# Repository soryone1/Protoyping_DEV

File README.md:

# Protoyping_DEV
This is for Prototyping Electronic Devices

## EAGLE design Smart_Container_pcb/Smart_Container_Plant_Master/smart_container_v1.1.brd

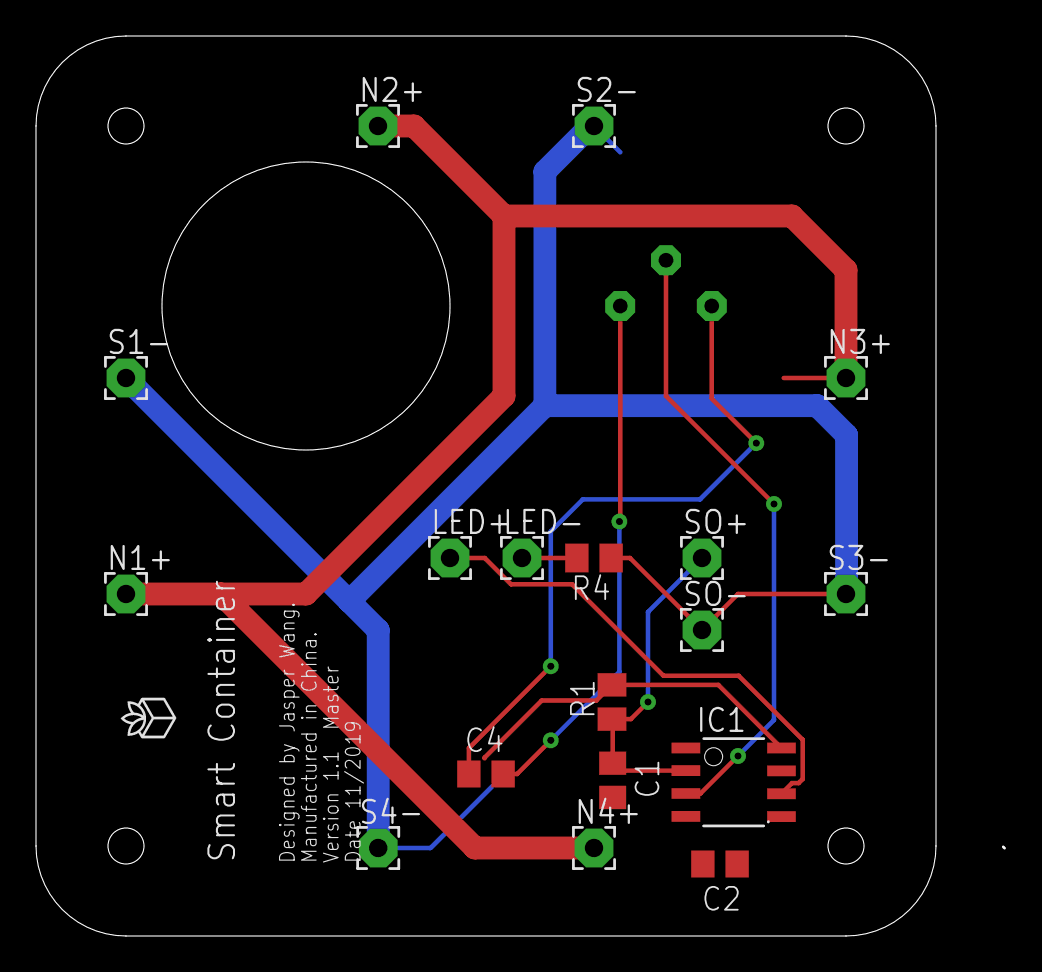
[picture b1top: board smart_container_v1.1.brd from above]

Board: 2 copper layers, 53.7 x 49.8 mm, 19 parts (1 on the bottom side), 9 nets.

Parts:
C1, C2, C4: 0.1uF; C0805
IC1: TINY13-20SSU; 8S1
LED+: 2,15/1,0
LED-: 2,15/1,0
N1+, N2+, N3+, N4+: 2,15/1,0
R1: 10k; M0805
R3: 10k; 3386P
R4: 220; M0805
S1-, S2-, S3-, S4-: 2,15/1,0
SO+: 2,15/1,0
SO-: 2,15/1,0

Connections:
GND: C1.2, C2.2, IC1.4, R4.1, S1-.1, S2-.1, S3-.1, S4-.1, SO-.1
L0: IC1.6, LED+.1
N4+: C4.1, R3.3
unnamed: LED-.1, R4.2
unnamed: C1.1, IC1.2, R1.1, SO+.1
S4-: C4.2, R3.1
S$1: IC1.8, R1.2
VCC: N1+.1, N2+.1, N3+.1, N4+.1
VR0: IC1.3, R3.2

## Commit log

2019-09-25 Create LED_Cube.ino
    LED_Cube
2019-09-25 test git
2019-10-02 add led cube and esp32
2019-11-01 add all files
2019-11-01 add file lastest
2019-11-03 add attiny85
2019-11-10 add files
2019-11-10 revise the code
2019-11-13 update files
2019-11-20 add cap to circuit
